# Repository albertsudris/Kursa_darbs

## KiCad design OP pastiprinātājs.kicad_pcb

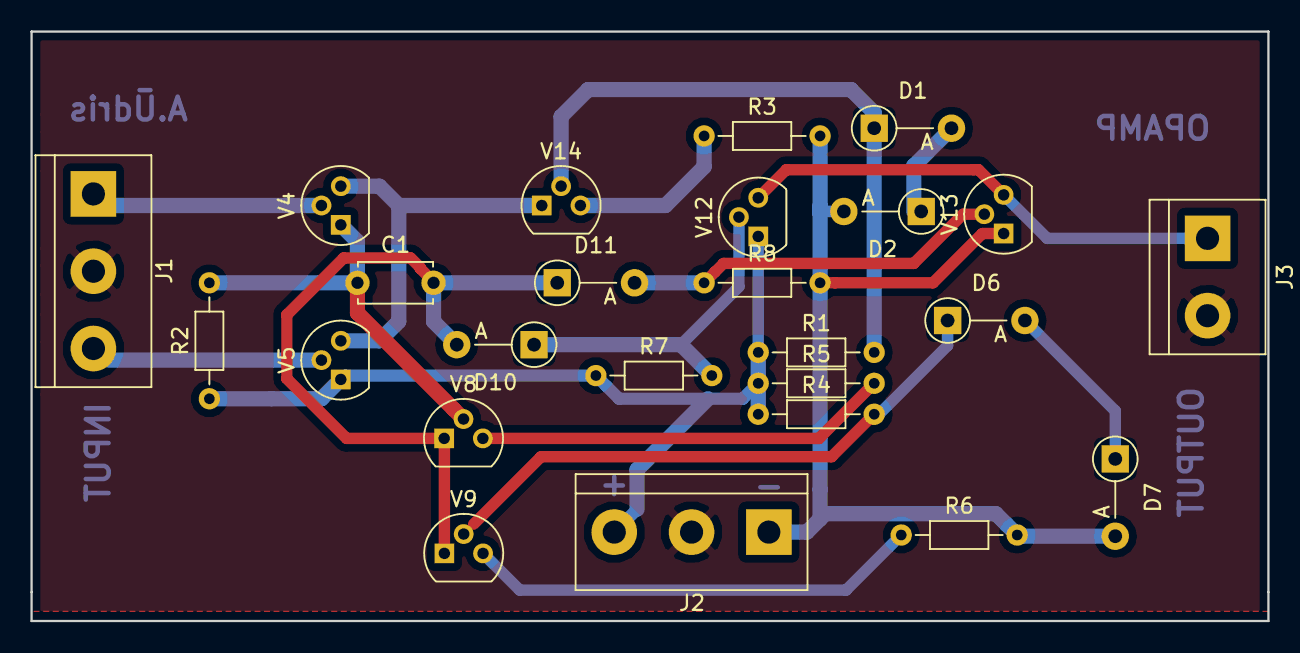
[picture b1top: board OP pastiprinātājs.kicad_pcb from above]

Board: 2 copper layers, 81.3 x 38.7 mm, 25 parts (0 on the bottom side), 18 nets.

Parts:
C1: 100p; C_Disc_D4.7mm_W2.5mm_P5.00mm
D1, D2, D6, D7, D10, D11: 1N914; D_A-405_P5.08mm_Vertical_AnodeUp
J1, J2: Conn_01x03_Male; TerminalBlock_bornier-3_P5.08mm
J3: Conn_01x02_Male; TerminalBlock_bornier-2_P5.08mm
R1, R4, R7, R8: 12k; R_Axial_DIN0204_L3.6mm_D1.6mm_P7.62mm_Horizontal
R2: 1k; R_Axial_DIN0204_L3.6mm_D1.6mm_P7.62mm_Horizontal
R3, R6: 300; R_Axial_DIN0204_L3.6mm_D1.6mm_P7.62mm_Horizontal
R5: 100; R_Axial_DIN0204_L3.6mm_D1.6mm_P7.62mm_Horizontal
V4, V5, V9, V12, V14: BC547; TO-92
V8, V13: BC557; TO-92

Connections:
Earth: J1.2, J2.2, J3.2
unnamed: C1.1, R2.2, V4.2, V8.1
unnamed: C1.2, D10.2, D11.1, V8.2, V9.2
unnamed: D1.1, R1.2, V14.1
unnamed: D1.2, D2.1
unnamed: D2.2, D7.2, J2.1, R3.2, R6.2, R8.2, V13.2
unnamed: D6.1, R4.2, V9.1
unnamed: D6.2, D7.1
unnamed: D10.1, R7.2, V12.1
unnamed: D11.2, R8.1, V13.1
unnamed: J1.1, V4.1
unnamed: J1.3, V5.1
unnamed: J2.3, R1.1, R2.1, R4.1, R5.1, R7.1, V5.2, V12.2
unnamed: J3.1, V12.3, V13.3
unnamed: R3.1, V14.3
unnamed: R5.2, V8.3
unnamed: R6.1, V9.3
unnamed: V4.3, V5.3, V14.2

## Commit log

2019-06-12 kursa_darbs
